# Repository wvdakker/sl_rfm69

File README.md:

RFM69 blade for the streamline series

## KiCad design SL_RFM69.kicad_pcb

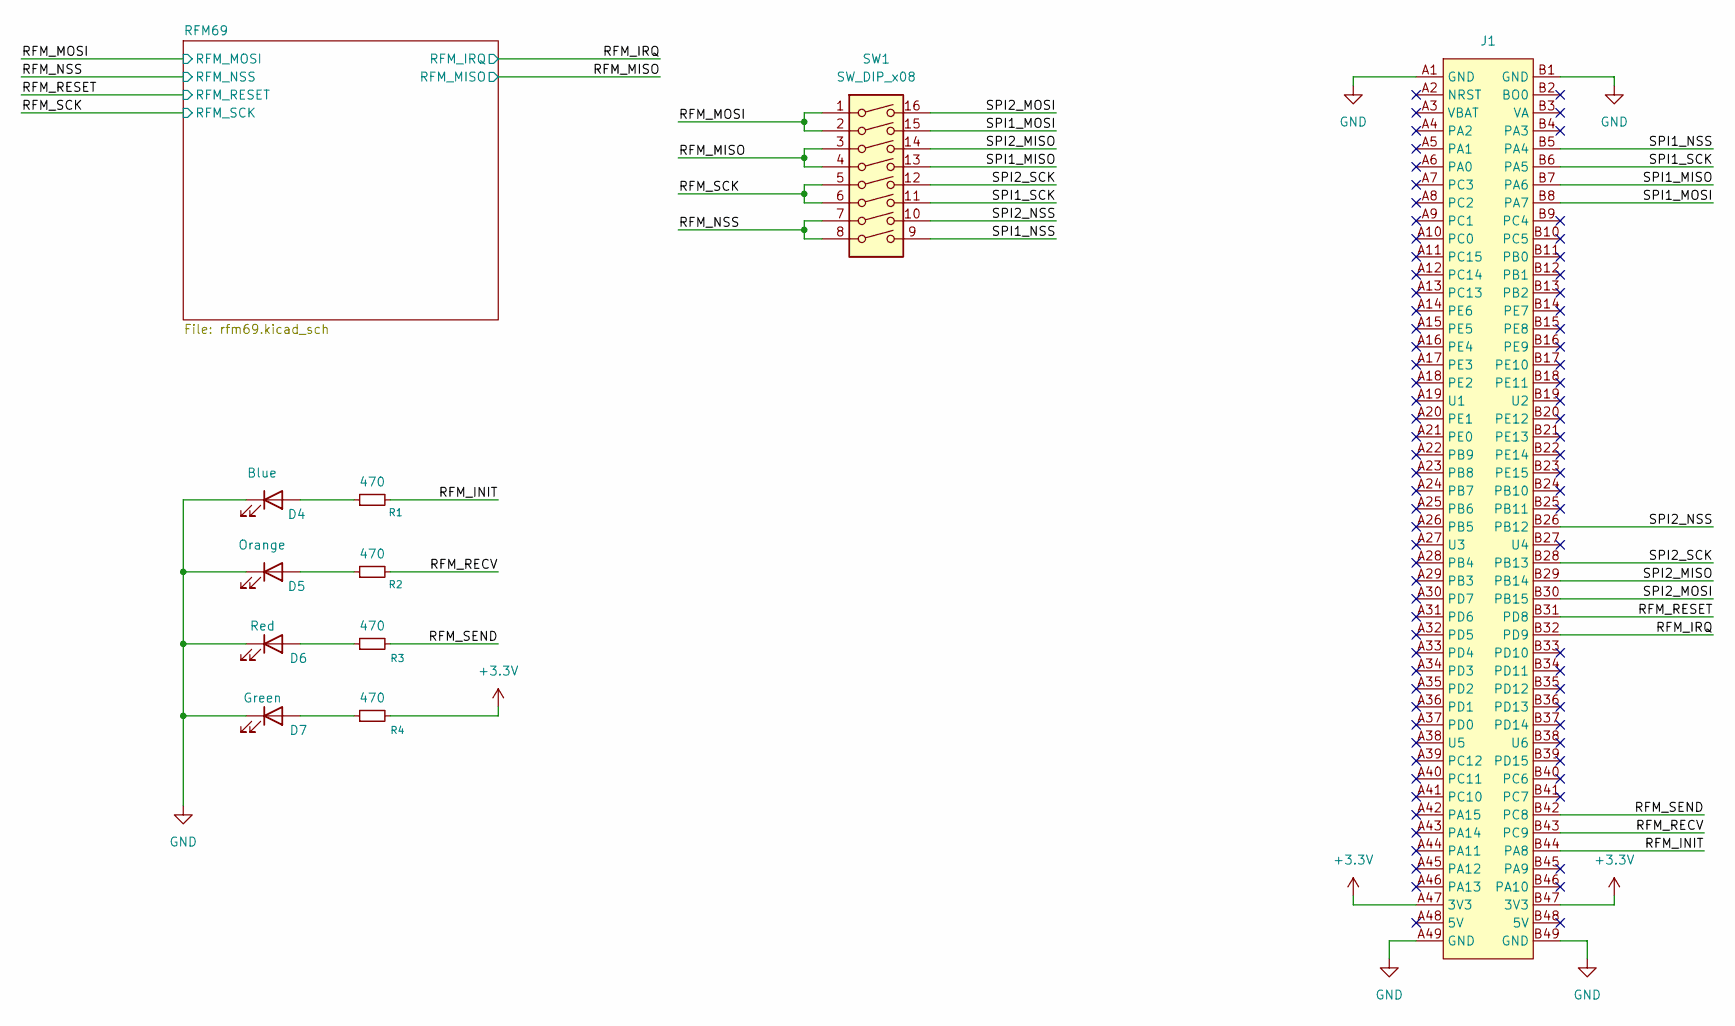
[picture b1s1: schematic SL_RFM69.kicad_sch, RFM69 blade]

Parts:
D4: Blue; LED_0805_2012Metric
D5: Orange; LED_0805_2012Metric
D6: Red; LED_0805_2012Metric
D7: Green; LED_0805_2012Metric
J1: SL_BOARD
R1, R2, R3, R4: 470; LED_0805_2012Metric
SW1: SW_DIP_x08; SW_DIP_SPSTx08_Slide_KingTek_DSHP08TJ_W5.25mm_P1.27mm_JPin; LCSC C559170

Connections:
+3.3V: J1.A47 (3V3), J1.B47 (3V3), R4.2; also elsewhere on the board
/RFM_INIT: J1.B44 (PA8), R1.2
/RFM_IRQ: J1.B32 (PD9); also elsewhere on the board
/RFM_MISO: SW1.3, SW1.4; also elsewhere on the board
/RFM_MOSI: SW1.1, SW1.2; also elsewhere on the board
/RFM_NSS: SW1.7, SW1.8; also elsewhere on the board
/RFM_RECV: J1.B43 (PC9), R2.2
/RFM_RESET: J1.B31 (PD8); also elsewhere on the board
/RFM_SCK: SW1.5, SW1.6; also elsewhere on the board
/RFM_SEND: J1.B42 (PC8), R3.2
/SPI1_MISO: J1.B7 (PA6), SW1.13
/SPI1_MOSI: J1.B8 (PA7), SW1.15
/SPI1_NSS: J1.B5 (PA4), SW1.9
/SPI1_SCK: J1.B6 (PA5), SW1.11
/SPI2_MISO: J1.B29 (PB14), SW1.14
/SPI2_MOSI: J1.B30 (PB15), SW1.16
/SPI2_NSS: J1.B26 (PB12), SW1.10
/SPI2_SCK: J1.B28 (PB13), SW1.12
GND: D4.1 (K), D5.1 (K), D6.1 (K), D7.1 (K), J1.A1 (GND), J1.A49 (GND), J1.B1 (GND), J1.B49 (GND); also elsewhere on the board
unnamed: D4.2 (A), R1.1
unnamed: D5.2 (A), R2.1
unnamed: D6.2 (A), R3.1
unnamed: D7.2 (A), R4.1

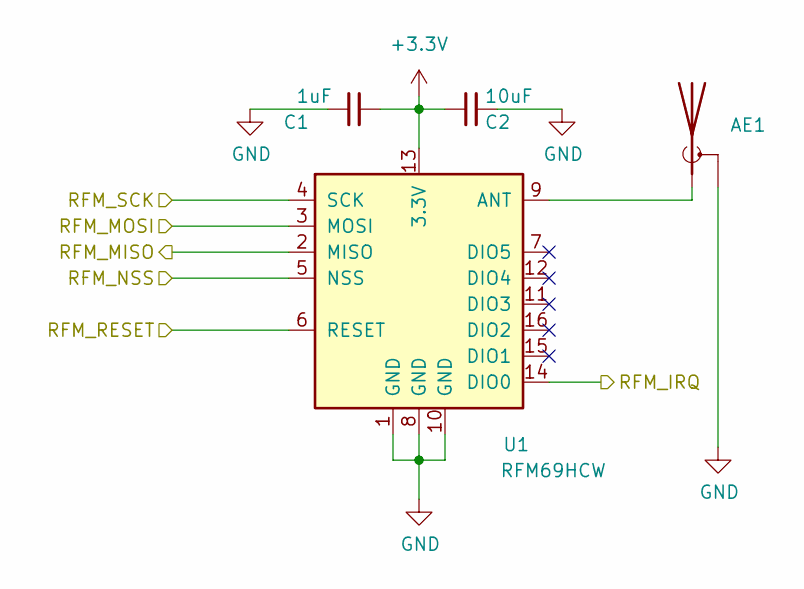
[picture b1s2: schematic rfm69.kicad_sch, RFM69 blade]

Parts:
AE1: Antenna_Shield; SMA_Amphenol_132289_EdgeMount; LCSC C88374
C1: 1uF; C_0402_1005Metric; LCSC C52923
C2: 10uF; C_0402_1005Metric; LCSC C15525
U1: RFM69HCW; HOPERF_RFM9XW_SMD

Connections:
+3.3V: C1.1, C2.2, U1.13 (3.3V); also elsewhere on the board
/RFM_IRQ: U1.14 (DIO0); also elsewhere on the board
/RFM_MISO: U1.2 (MISO); also elsewhere on the board
/RFM_MOSI: U1.3 (MOSI); also elsewhere on the board
/RFM_NSS: U1.5 (NSS); also elsewhere on the board
/RFM_RESET: U1.6 (RESET); also elsewhere on the board
/RFM_SCK: U1.4 (SCK); also elsewhere on the board
GND: AE1.2 (Shield), C1.2, C2.1, U1.1 (GND), U1.8 (GND), U1.10 (GND); also elsewhere on the board
unnamed: AE1.1 (A), U1.9 (ANT)

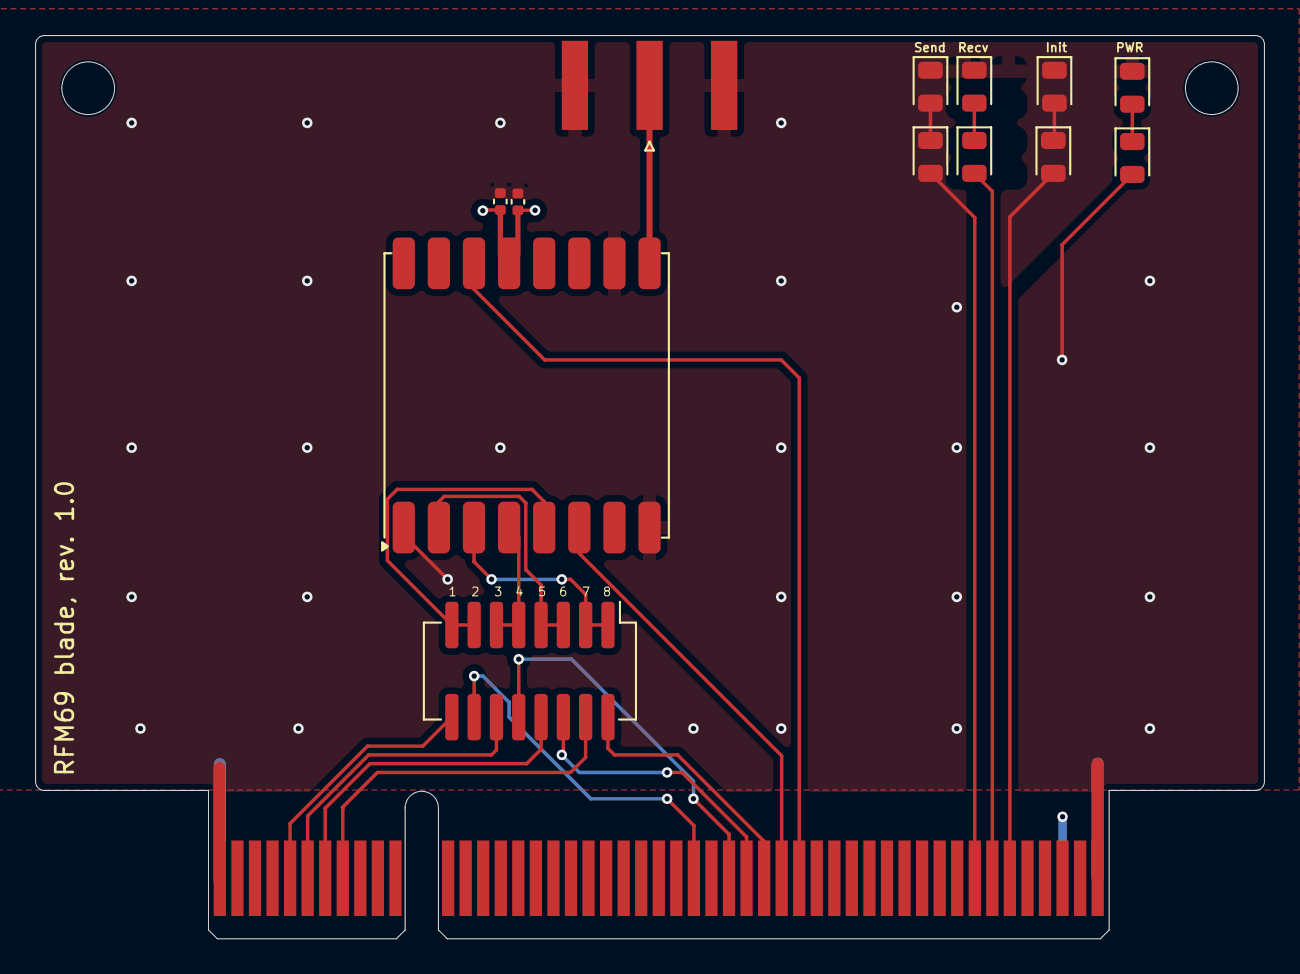
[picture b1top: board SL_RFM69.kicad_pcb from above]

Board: 4 copper layers, 70.0 x 51.4 mm, 14 parts (0 on the bottom side), 24 nets.
